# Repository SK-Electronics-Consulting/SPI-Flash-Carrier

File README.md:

# SPI Flash Development Board

## Background
This is a simple board for developing an SPI Flash chip.  

## Supported chips
Generally speaking, a 3x2mm 8-pin DFN will work on this board. The pins should be checked to match up.

* W25Q16JQUXIQ (Developed against)

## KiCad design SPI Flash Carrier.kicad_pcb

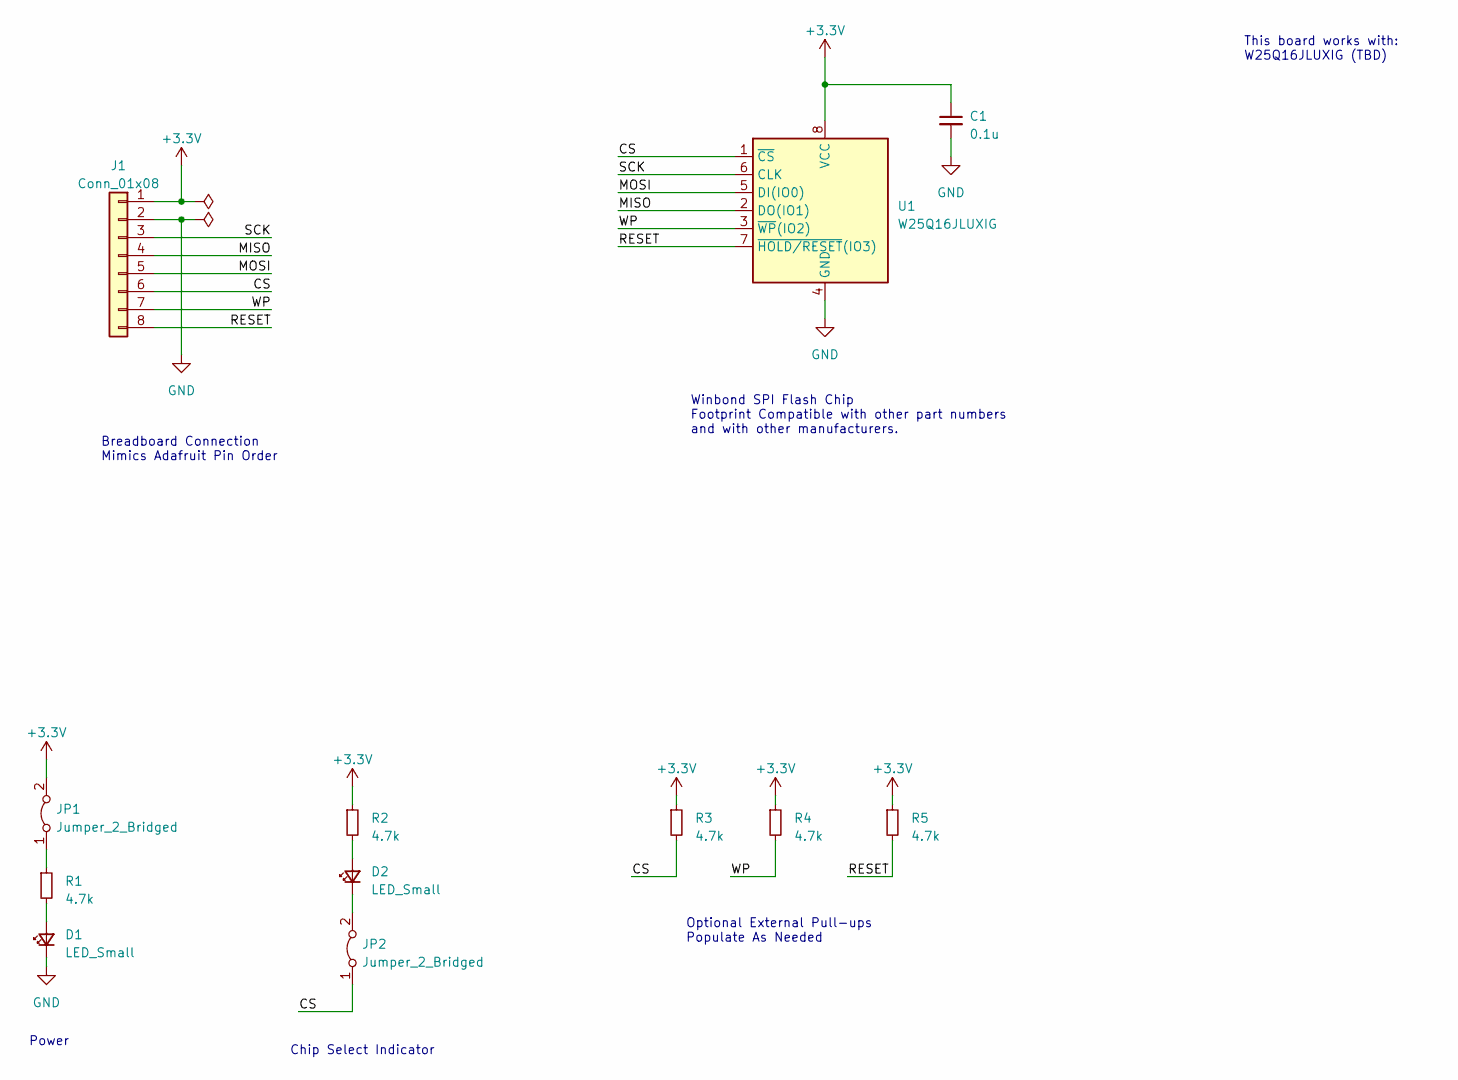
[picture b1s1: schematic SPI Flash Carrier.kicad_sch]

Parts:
C1: 0.1u; C_0402_1005Metric_Pad0.74x0.62mm_HandSolder
D1, D2: LED_Small; LED_0603_1608Metric_Pad1.05x0.95mm_HandSolder
J1: Conn_01x08; PinHeader_1x08_P2.54mm_Vertical
JP1, JP2: Jumper_2_Bridged; SolderJumper-2_P1.3mm_Bridged2Bar_RoundedPad1.0x1.5mm
R1, R2, R3, R4, R5: 4.7k; R_0402_1005Metric_Pad0.72x0.64mm_HandSolder
U1: W25Q16JLUXIG; DFN-8-1EP_3x2mm_P0.5mm_EP1.3x1.5mm

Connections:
+3.3V: C1.1, J1.1, JP1.2 (B), R2.1, R3.1, R4.1, R5.1, U1.8 (VCC)
/CS: J1.6, JP2.1 (A), R3.2, U1.1 (~CS)
/MISO: J1.4, U1.2 (DO(IO1))
/MOSI: J1.5, U1.5 (DI(IO0))
/RESET: J1.8, R5.2, U1.7 (~HOLD/RESET(IO3))
/SCK: J1.3, U1.6 (CLK)
/WP: J1.7, R4.2, U1.3 (~WP(IO2))
GND: C1.2, D1.1 (K), J1.2, U1.4 (GND)
unnamed: D1.2 (A), R1.2
unnamed: D2.2 (A), R2.2
unnamed: D2.1 (K), JP2.2 (B)
unnamed: JP1.1 (A), R1.1

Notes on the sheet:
This board works with: W25Q16JLUXIG (TBD)
Winbond SPI Flash Chip Footprint Compatible with other part numbers and with other manufacturers.
Power
Breadboard Connection Mimics Adafruit Pin Order
Chip Select Indicator
Optional External Pull-ups Populate As Needed

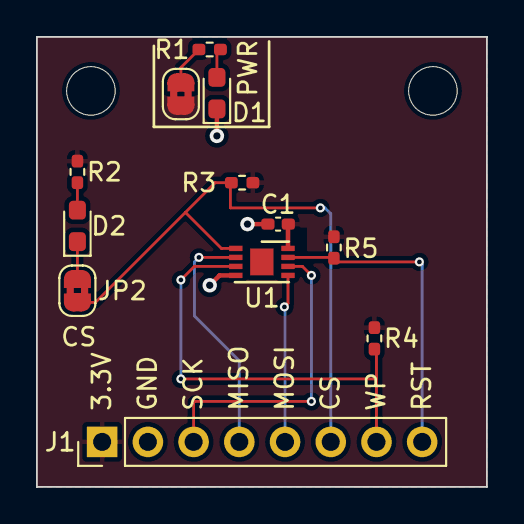
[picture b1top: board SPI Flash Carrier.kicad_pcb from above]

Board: 2 copper layers, 25.0 x 25.0 mm, 12 parts (0 on the bottom side), 12 nets.

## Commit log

2023-04-15 Update gitignore for backups
2023-04-15 First version of board
2023-04-15 Added README with basic info.
2023-04-15 Cleaned up PCB fab and generated gerbers
